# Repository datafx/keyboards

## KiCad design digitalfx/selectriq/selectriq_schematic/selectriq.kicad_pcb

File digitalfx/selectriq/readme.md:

# digitalfx Selectric

65% pcb IBM Selectric converted with a modified KBDFans KBD67 rev2

Keyboard Maintainer: [digitalfx](https://github.com/datafx)  
Hardware Supported: Modified KBD67v2 PCB  
Hardware Availability: custom

Make example for this keyboard (after setting up your build environment):

    make digitalfx/selectriq:default

See the [build environment setup](https://docs.qmk.fm/#/getting_started_build_tools) and the [make instructions](https://docs.qmk.fm/#/getting_started_make_guide) for more information. Brand new to QMK? Start with our [Complete Newbs Guide](https://docs.qmk.fm/#/newbs).

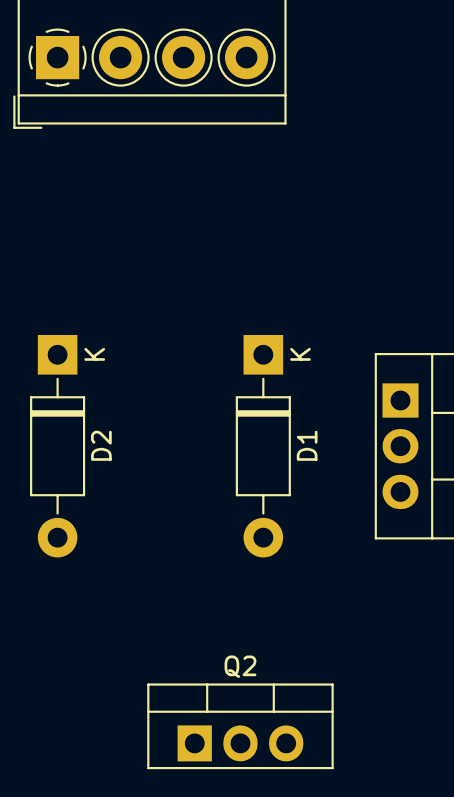
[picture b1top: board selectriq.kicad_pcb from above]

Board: 2 copper layers, 5 parts (0 on the bottom side), 6 nets, no tracks yet.

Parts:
D1, D2: 1N4007; D_DO-41_SOD81_P10.16mm_Horizontal
J3: Screw_Terminal_01x04; TerminalBlock_4Ucon_1x04_P3.50mm_Horizontal
Q1, Q2: TIP120; TO-220-3_Vertical

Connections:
unnamed: D1.1, D2.1, J3.1
unnamed: D1.2, Q1.2
unnamed: D2.2, Q2.2
unnamed: J3.2, Q1.3, Q2.3
unnamed: J3.3, Q2.1
unnamed: J3.4, Q1.1

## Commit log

2021-05-03 remove extra directory
2021-05-03 remove extra file
2021-05-09 add wpm counter to oled
2021-05-10 more oled updates
2021-05-10 code cleanup
2021-05-10 tapdance and keymap updates
2021-05-14 removed vial encoder support and hardcoded encoder settings
2021-05-15 minor changes to oled
2021-07-25 Add support for KBD67 mkii rgb v3
2021-07-25 update kbd67 readme with v3 info
2021-07-25 typo
2021-07-26 Fix v3 bootloader for 6K size
    It seems that KBDFans used 6K bootloader.
2021-07-26 correct v3 readme
2021-07-28 kbd67 mkiirgb v3 vial rgb support
2021-08-23 add murphpad
2021-08-26 dz60
2021-10-17 New projects added
2021-10-17 new custom build
2021-10-22 mb44 vial firmware
2021-10-29 Updated solenoid control
2021-10-29 update keymap and add vial support
2021-10-29 fix unlock combo
2021-10-30 add schematic
2021-12-21 Add fjlabs kf87 with rgbmatrix support
2021-12-21 add kf87 via json
2022-02-07 Fixed led_config ordering
    start counting with 0 instead of 1...ugh
2022-02-07 add VIAL support
2022-02-19 model m add and kf87 changes
2022-03-04 Add VIA/VIAL support, add note about LED on Teensy causing problems.
2022-03-07 hammerspoon integration for mb44
2022-03-13 Add RGB LEDs to Model M
2022-03-13 Update documentation
2023-01-17 FJlabs kf87 cleanup
